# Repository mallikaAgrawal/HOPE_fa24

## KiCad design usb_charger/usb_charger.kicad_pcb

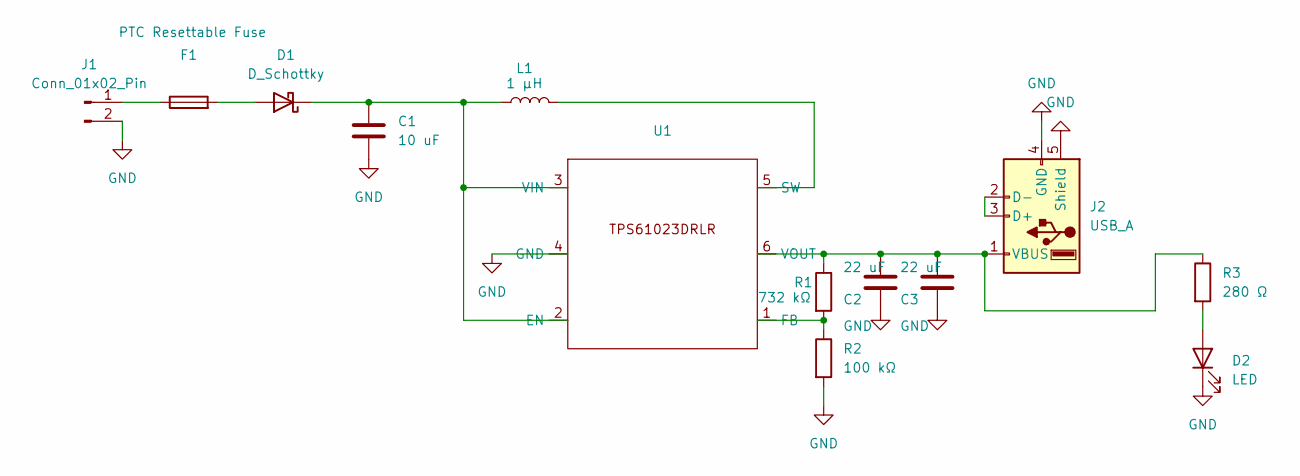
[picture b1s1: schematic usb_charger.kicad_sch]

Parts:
C1: 10 uF; C_0805_2012Metric
C2, C3: 22 uF; C_0805_2012Metric
D1: D_Schottky; D_SOD-123
D2: LED; LED_ROHM_SMLVN6
F1: PTC Resettable Fuse; Fuse_1812_4532Metric_Pad1.30x3.40mm_HandSolder
J1: Conn_01x02_Pin; PinHeader_1x02_P2.54mm_Vertical
J2: USB_A; 87520_0010BLF
L1: 1 µH; L_Wurth_WE-LQSH-4020
R1: 732 kΩ; R_0603_1608Metric
R2: 100 kΩ; R_0603_1608Metric
R3: 280 Ω; R_0805_2012Metric
U1: TPS61023DRLR

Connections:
GND: C1.2, C2.2, C3.2, D2.1 (K), J1.2, J2.4 (GND), J2.5 (Shield), R2.2, U1.4 (GND)
unnamed: D1.2 (A), F1.2
unnamed: C1.1, D1.1 (K), L1.1, U1.2 (EN), U1.3 (VIN)
unnamed: D2.2 (A), R3.2
unnamed: F1.1, J1.1
unnamed: J2.2 (D-), J2.3 (D+)
unnamed: C2.1, C3.1, J2.1 (VBUS), R1.1, R3.1, U1.6 (VOUT)
unnamed: R1.2, R2.1, U1.1 (FB)
unnamed: L1.2, U1.5 (SW)

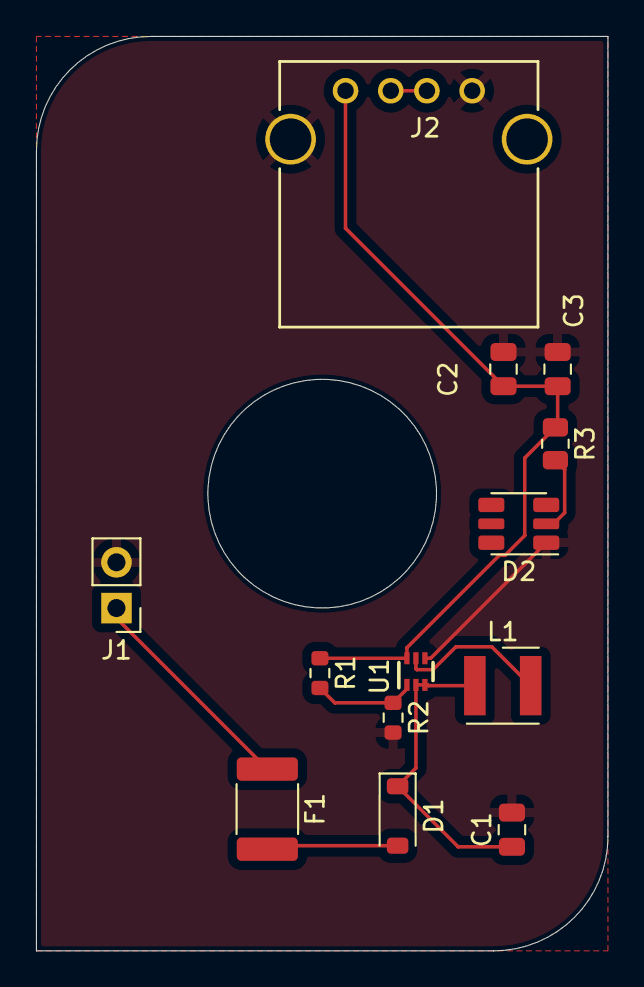
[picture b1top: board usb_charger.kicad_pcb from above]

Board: 2 copper layers, 31.8 x 50.8 mm, 13 parts (0 on the bottom side), 9 nets.

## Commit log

2024-09-04 lab 1 completed
2024-10-10 finished usb charger layout
